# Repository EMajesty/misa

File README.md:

<h1 align="center">MISA</h1>

<p align="center">
68k SBC somewhat inspired by the Lisa and the Mac, and similar projects around the net.
</p>

<p align="center">
MC68HC000P16 (at 4/8/16 MHz)
<br />
1MB ROM (2x SST39SF040)
<br />
1MB SRAM (2x AS6C4008-55PCN)
<br />
ATF1508 CPLD for glue
<br />
UART
<br />
CF card
<br />
Monochrome display
<br />
Audio with YM2151?
<br />
Keyboard?
<br />
Wifi with WizFi360???
</p>

### TODO

- [ ] HW proto
- [ ] PLD logic
- [ ] Monitor program
- [ ] UART stuff
- [ ] Display stuff
- [x] Font 
- [ ] Input stuff
- [ ] FAT16/VFAT 
- [ ] File manager
- [ ] A beep
- [ ] Text editor
- [ ] Terminal emulator
- [ ] Lisp interpreter
- [ ] Doom
- [ ] ?????
- [ ] Multitasking kernel

### Docs

[68000 Hardware Manual](https://bitsavers.org/pdf/peripheralTechnology/68000_Hardware_Manual.pdf)

[M68000 User's Manual](https://www.nxp.com/docs/en/reference-manual/MC68000UM.pdf)

### BOM

| Ref | Part | Qty | Package | Datasheet | Notes |
|---|---|---|---|---|---|
||MC68HC000|1|DIP64/PLCC68|[Datasheet](https://igspgm.com/repairs/MC68HC000.pdf)|MPU|
||YM2151|1|DIP24|[Datasheet](https://retrocdn.net/images/1/1c/YM2151_datasheet.pdf)<br/>[Application manual](https://retrocdn.net/images/9/9c/YM2151_Application_Manual.pdf)|Sound|
||YM3012|1|DIP16|[Datasheet](https://datasheet4u.com/pdf-down/Y/M/3/YM3012-Yamaha.pdf)|DAC|
||TDA2822M|1|DIP8|[Datasheet](https://www.mouser.com/catalog/specsheets/stmicroelectronics_cd00000134.pdf)|Power amp|
||AS6C4008-55PCN|2|DIP32|[Datasheet](https://eu.mouser.com/datasheet/3/893/1/AS6C4008.pdf)|SRAM|
||SST39SF040|2|PLCC32|[Datasheet](https://ww1.microchip.com/downloads/aemDocuments/documents/MPD/ProductDocuments/DataSheets/SST39SF010A-SST39SF020A-SST39SF040-Data-Sheet-DS20005022.pdf)|ROM|
||ATF1508AS|1|PLCC84|[Datasheet](https://ww1.microchip.com/downloads/en/DeviceDoc/doc0784.pdf)|CPLD|
||MC68681FN|1|PLCC44|[Datasheet](https://www.microelectronicash.com/downloads/MC68681P.pdf)<br/>[AN-0899](https://www.bitsavers.org/components/motorola/_appNotes/AN-0899_A_Terminal_Interface,_Printer...for_an_MC68000-Based_System_using_the_MC68681_DUART.pdf)|DUART|
||NE555P|1|DIP8|[Datasheet](https://www.ti.com/lit/ds/symlink/se555.pdf?HQS=dis-dk-null-digikeymode-dsf-pf-null-wwe&ts=1771745013638&ref_url=https%253A%252F%252Fwww.ti.com%252Fgeneral%252Fdocs%252Fsuppproductinfo.tsp%253FdistId%253D10%2526gotoUrl%253Dhttps%253A%252F%252Fwww.ti.com%252Flit%252Fgpn%252Fse555)||
||SN74HC05N|1|DIP14|[Datasheet](https://www.ti.com/lit/ds/symlink/sn74hc05.pdf?HQS=dis-dk-null-digikeymode-dsf-pf-null-wwe&ts=1771768334330&ref_url=https%253A%252F%252Fwww.ti.com%252Fgeneral%252Fdocs%252Fsuppproductinfo.tsp%253FdistId%253D10%2526gotoUrl%253Dhttps%253A%252F%252Fwww.ti.com%252Flit%252Fgpn%252Fsn74hc05)||
||SN74HCT74N|1|DIP14|[Datasheet](https://www.ti.com/lit/ds/symlink/sn74hct74.pdf?HQS=dis-dk-null-digikeymode-dsf-pf-null-wwe&ts=1771757308194&ref_url=https%253A%252F%252Fwww.ti.com%252Fgeneral%252Fdocs%252Fsuppproductinfo.tsp%253FdistId%253D10%2526gotoUrl%253Dhttps%253A%252F%252Fwww.ti.com%252Flit%252Fgpn%252Fsn74hct74)||
||16 MHz oscillator|1|DIP8|[Datasheet](https://www.ctscorp.com/Files/DataSheets/Passives/FCP/Clock-Oscillators/clock-ocillators-MXO45_MXO45HS-datasheet.pdf)||
||3.6864 MHz oscillator|1|DIP8|[Datasheet](https://www.ctscorp.com/Files/DataSheets/Passives/FCP/Clock-Oscillators/clock-ocillators-MXO45_MXO45HS-datasheet.pdf)||
||WizFi360-CON|1||[Datasheet](https://docs.wiznet.io/pdf-viewer?file=%2Fassets%2Ffiles%2Fwizfi360_ds_v112_en-1495cb0bcb7e6583e492b1b8967f7fb4.pdf)|WIFI|
||5.7" 320240 RA8835|1||[Module](https://www.buydisplay.com/download/manual/ERM320240-1_Series_Datasheet.pdf)<br />[Controller](https://www.buydisplay.com/download/ic/RA8835.pdf)|Display|

### Memory map (RAM vectors + 2 MiB I/O)

| Region   | Start      | End        | Size   | Notes |
|---------|------------|------------|--------|-------|
| ROM     | 0x00000000 | 0x000FFFFF | 1 MiB  | 2x SST39SF040; contains reset vectors, monitor, bootloader; early startup runs from here. |
| Vectors | 0x00100000 | 0x001003FF | 1 KiB  | Vector table copied from ROM into RAM at boot; CPU configured to use RAM vectors.|
| RAM     | 0x00100000 | 0x001FFFFF | 1 MiB  | Same 1 MiB SRAM; low area holds vectors + kernel data, high end used for supervisor/user stacks and heap. |
| I/O     | 0x00E00000 | 0x00FFFFFF | 2 MiB  | CPLD‑decoded I/O window for UART, IDE/CF, keyboard, video, audio, WiFi, unused space.|
| Unused  | Everything else | -     | -      ||

### I/O submap (0x00E00000–0x00FFFFFF)

| Device   | CS        | Start      | End        | Size    | Bus width | Notes |
|---------|-----------|------------|------------|---------|-----------|-------|
| UART    | UART_CS   | 0x00E00000 | 0x00E00FFF | 4 KiB   | 8‑bit     | MC68681FN on D0–D7, RS0–RS3 from CPU A1–A4.|
| IDE / CF| IDE_CS0/1 | 0x00E01000 | 0x00E01FFF | 4 KiB   | 16‑bit    | 16‑bit data path via CPLD, command/control regs.|
| Keyboard| KBD_CS    | 0x00E02000 | 0x00E02FFF | 4 KiB   | 8‑bit     | Simple DATA/STATUS/CONTROL registers.|
| Video   | VID_CS    | 0x00E03000 | 0x00E03FFF | 4 KiB   | 8‑ or 16‑bit | RA8835 controller regs; framebuffer mapped elsewhere or via paging.|
| Audio   | AUD_CS    | 0x00E04000 | 0x00E04FFF | 4 KiB   | 8‑bit     | YM2151 register interface; DAC/analog path is fixed hardware, no CPU control.|
| WiFi    | WIFI_CS   | 0x00E05000 | 0x00E05FFF | 4 KiB   | 8‑bit     | WizFi360 memory‑mapped UART/command regs (future). |
| Unused  | –         | 0x00E06000 | 0x00FFFFFF | ~1.97 MiB | 8‑ or 16‑bit ||

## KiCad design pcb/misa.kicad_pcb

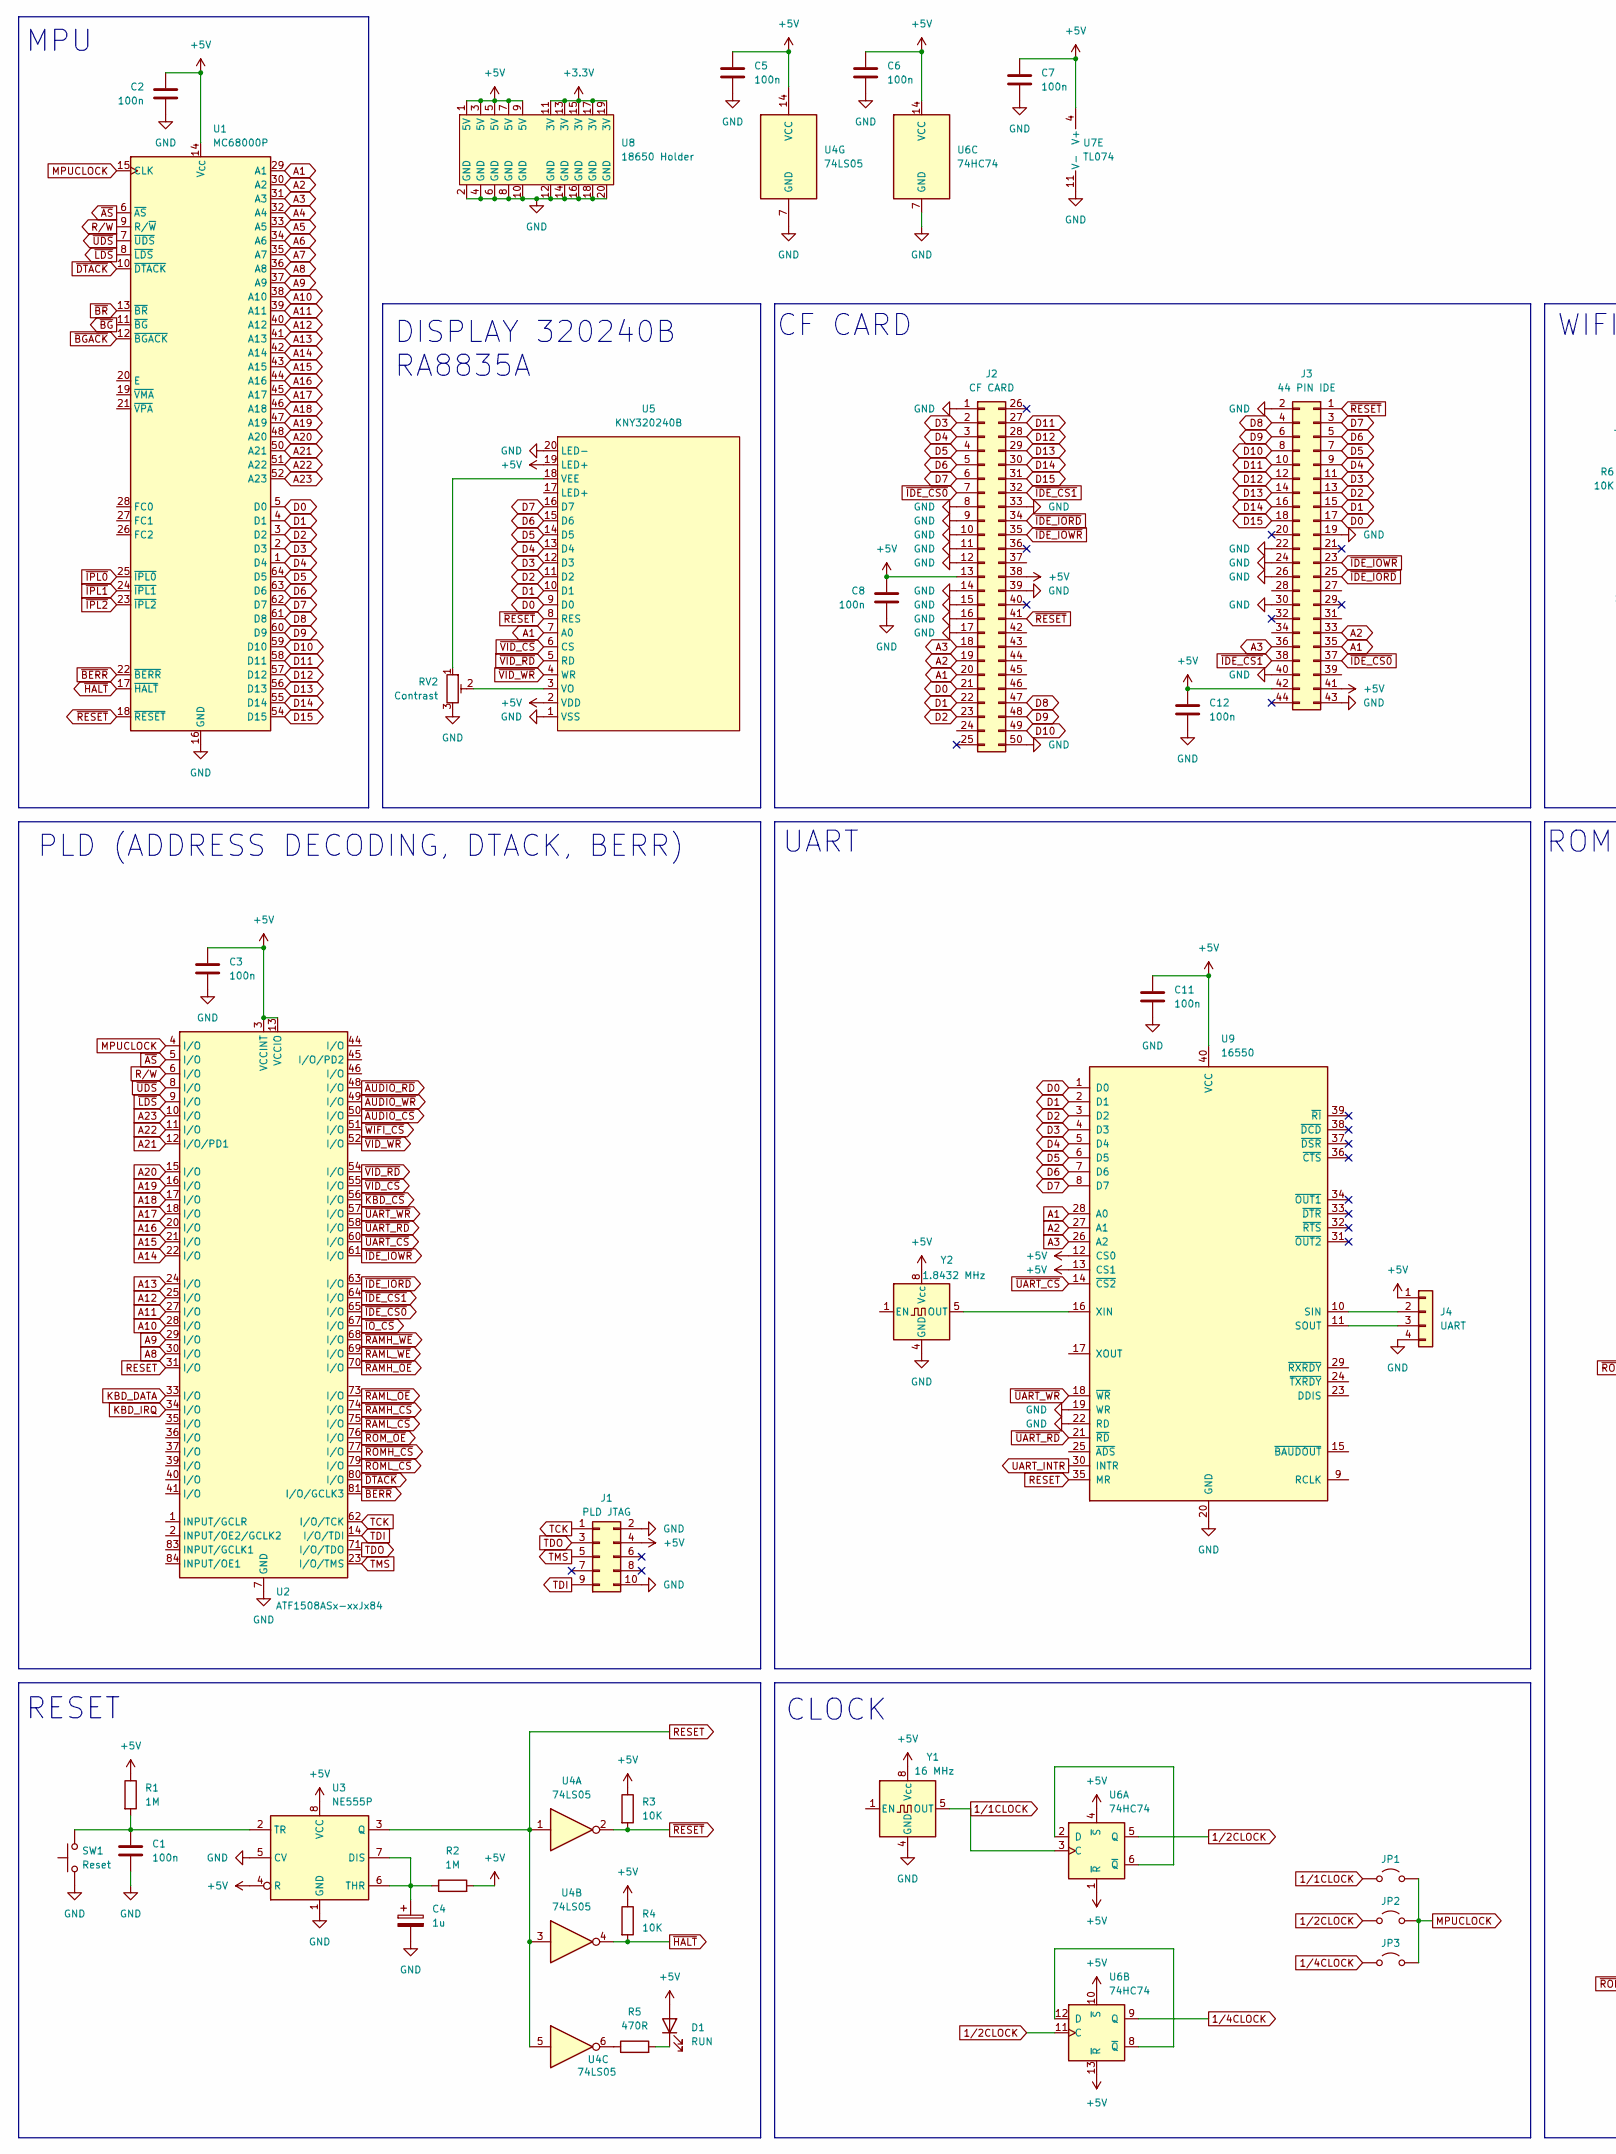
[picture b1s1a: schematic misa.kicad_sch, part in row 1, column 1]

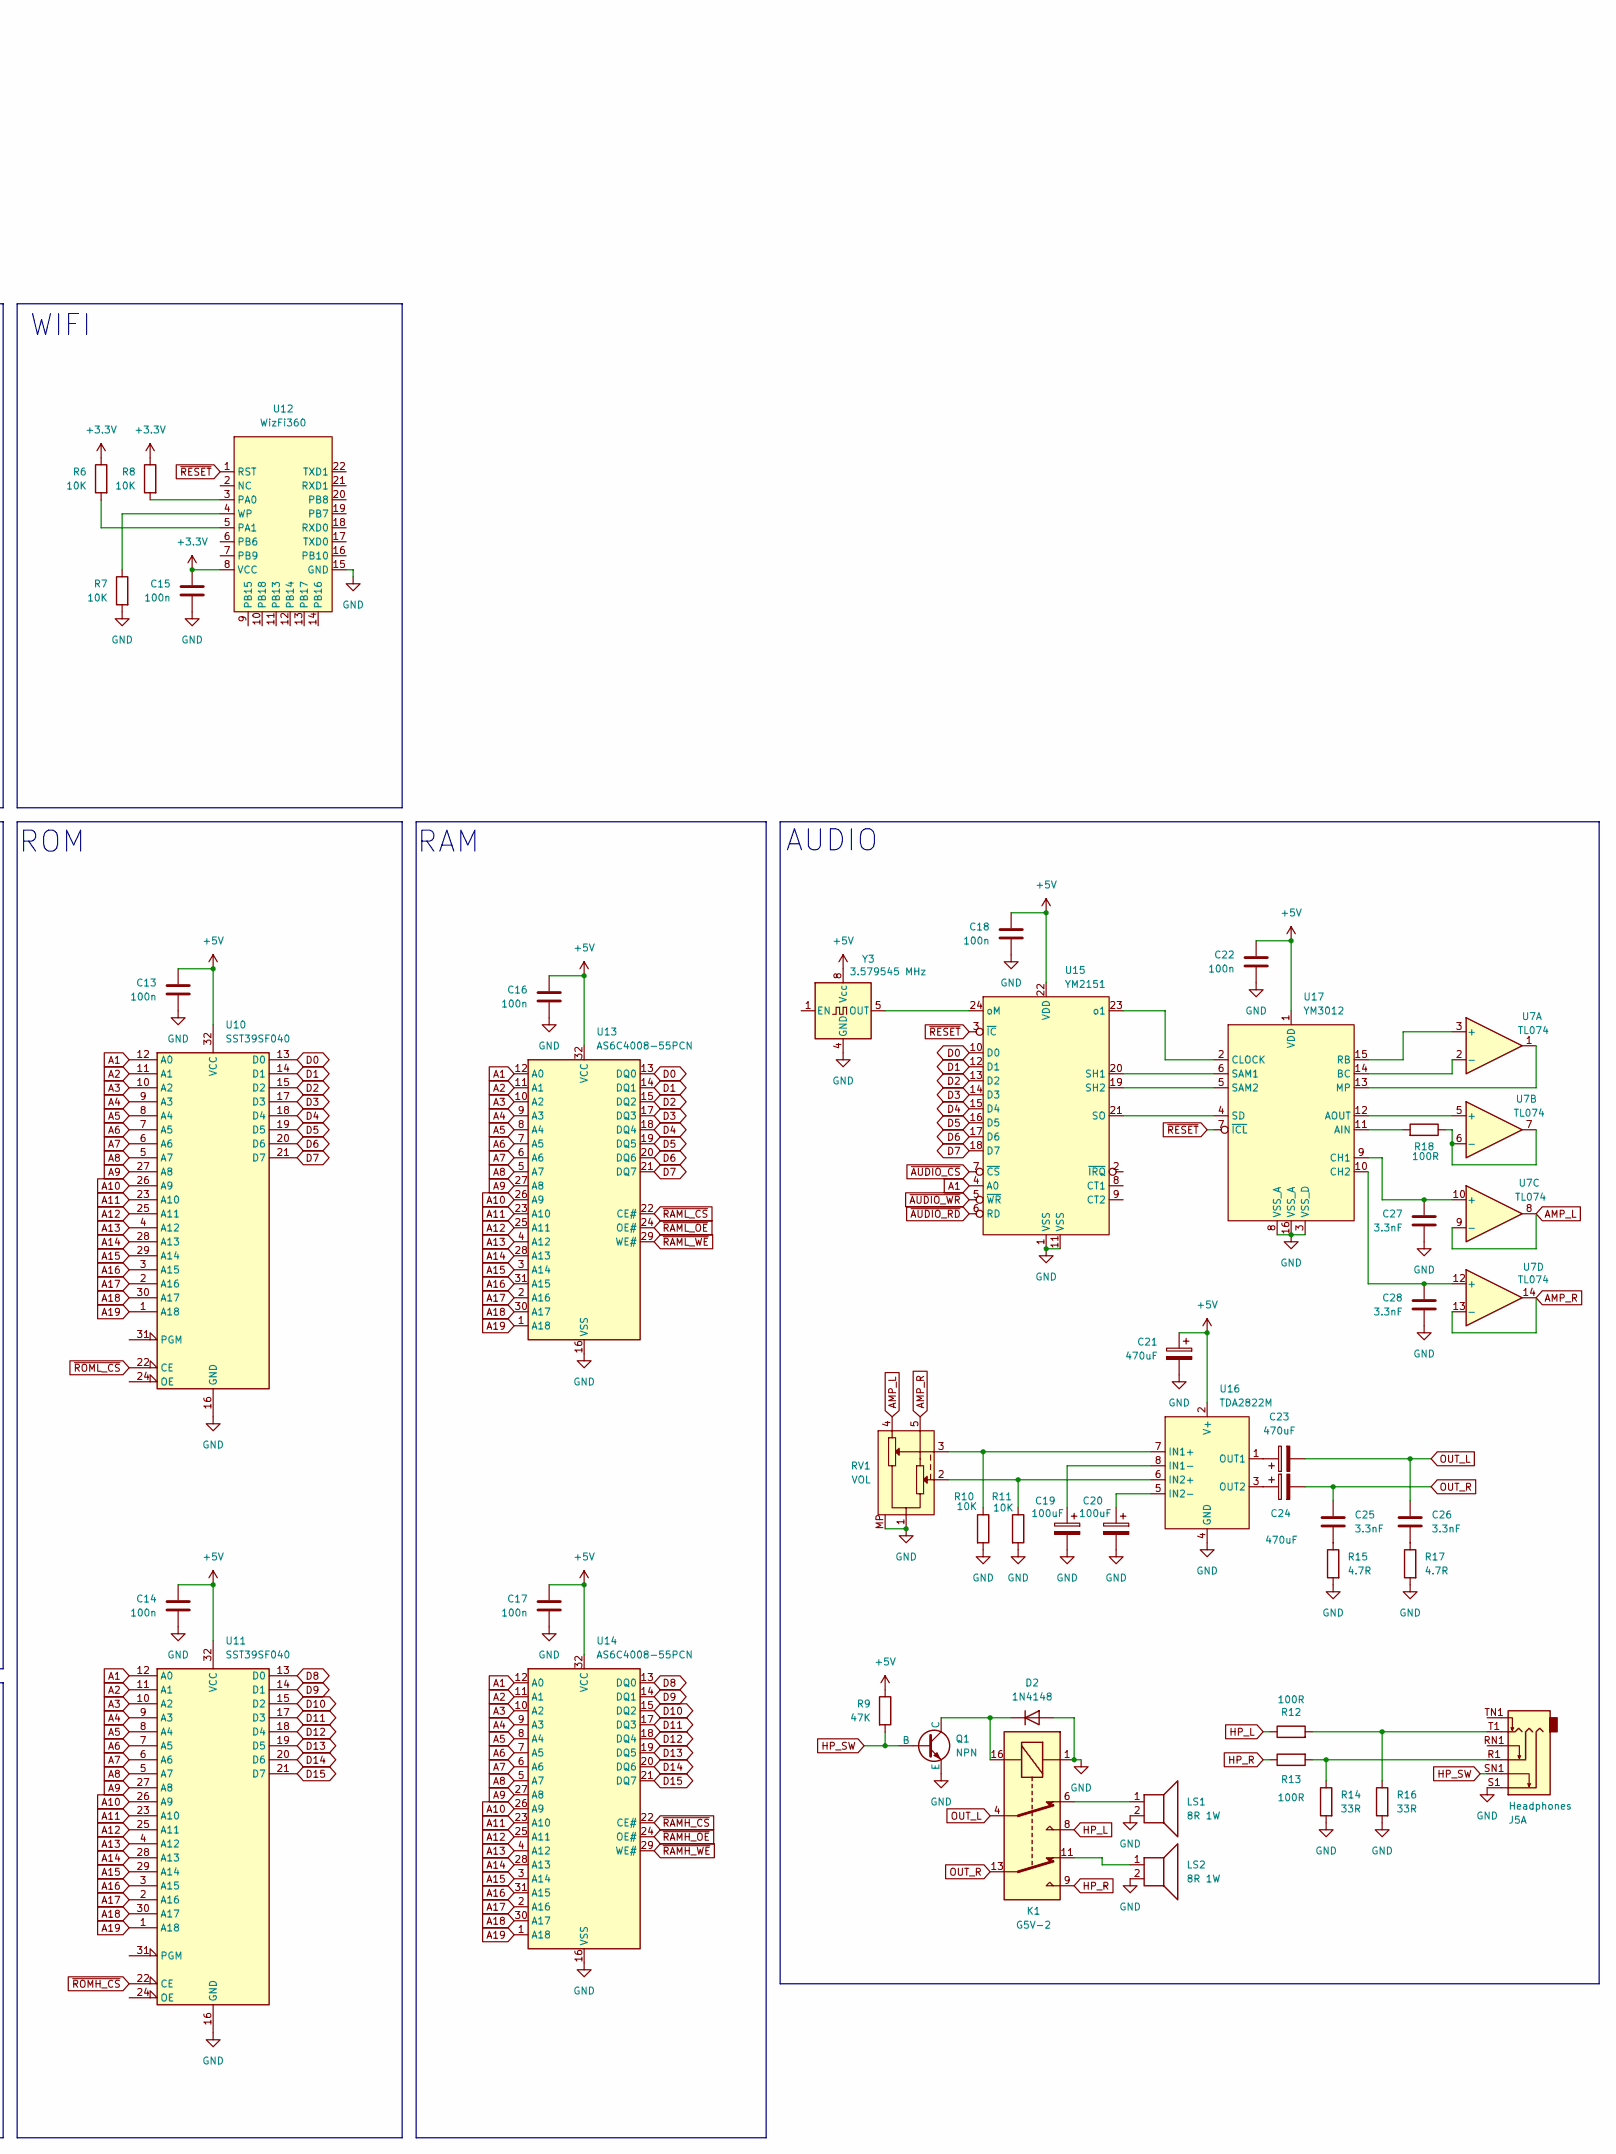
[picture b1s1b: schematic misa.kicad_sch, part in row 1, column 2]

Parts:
C1, C2, C3, C5, C6, C7, C8, C11, C12, C13, C14, C15, C16, C17, C18, C22: 100n; C_Rect_L7.0mm_W2.5mm_P5.00mm
C4: 1u; CP_Radial_D4.0mm_P2.00mm
C19, C20: 100uF; CP_Radial_D5.0mm_P2.50mm
C21, C23, C24: 470uF; CP_Radial_D6.3mm_P2.50mm
C25, C26, C27, C28: 3.3nF; C_Rect_L7.0mm_W2.5mm_P5.00mm
D1: RUN; LED_D3.0mm
D2: 1N4148; D_DO-35_SOD27_P7.62mm_Horizontal
J1: PLD JTAG; Pins_2x05_2.54mm_TH; Part Number 1-1002FBV0T
J2: CF CARD; CF_Card_Socket_PTH
J3: 44 PIN IDE; PinSocket_2x22_P2.54mm_Vertical
J4: UART; Pins_1x04_2.54mm_TH_SWD; Part Number 1-0401FBV0T
J5: Headphones; Jack_6.35mm_Neutrik_NMJ6HFD2-AU_Horizontal
JP1, JP2, JP3: Jumper_2_Open; PinHeader_1x02_P2.54mm_Vertical
K1: G5V-2; Relay_DPDT_Omron_G5V-2
LS1, LS2: 8R 1W; PinHeader_1x02_P2.54mm_Vertical
Q1: NPN; TO-92L_Inline_Wide
R1, R2: 1M; R_Axial_DIN0207_L6.3mm_D2.5mm_P7.62mm_Horizontal
R3, R4, R6, R7, R8, R10, R11: 10K; R_Axial_DIN0207_L6.3mm_D2.5mm_P7.62mm_Horizontal
R5: 470R; R_Axial_DIN0207_L6.3mm_D2.5mm_P7.62mm_Horizontal
R9: 47K; R_Axial_DIN0207_L6.3mm_D2.5mm_P7.62mm_Horizontal
R12, R13, R18: 100R; R_Axial_DIN0207_L6.3mm_D2.5mm_P7.62mm_Horizontal
R14, R16: 33R; R_Axial_DIN0207_L6.3mm_D2.5mm_P7.62mm_Horizontal
R15, R17: 4.7R; R_Axial_DIN0207_L6.3mm_D2.5mm_P7.62mm_Horizontal
RV1: VOL
RV2: Contrast
SW1: Reset
U1: MC68000P; PLCC-68_THT-Socket
U2: ATF1508ASx-xxJx84; PLCC-84_THT-Socket
U3: NE555P; DIP-8_W7.62mm
U4: 74LS05; DIP-14_W7.62mm_Socket_LongPads
U5: KNY320240B
U6: 74HC74; DIP-14_W7.62mm_Socket_LongPads
U7: TL074; DIP-14_W7.62mm_Socket_LongPads
U8: 18650 Holder; 18650_holder
U9: 16550; PLCC-44_THT-Socket
U10, U11: SST39SF040; PLCC-32_THT-Socket
U12: WizFi360; Untitled
U13, U14: AS6C4008-55PCN; DIP-32_W15.24mm
U15: YM2151; DIP-24_18.0mmx34.29mm_W15.24mm_Socket_LongPads
U16: TDA2822M; DIP-8_W7.62mm_Socket_LongPads
U17: YM3012; DIP-16_W7.62mm_Socket_LongPads
Y1: 16 MHz; Oscillator_DIP-8
Y2: 1.8432 MHz; Oscillator_DIP-8
Y3: 3.579545 MHz; Oscillator_DIP-8

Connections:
1/1CLOCK: JP1.1 (A), U6.3 (C), Y1.5 (OUT)
1/2CLOCK: JP2.1 (A), U6.5 (Q), U6.11 (C)
1/4CLOCK: JP3.1 (A), U6.9 (Q)
+3.3V: C15.1, R6.1, R8.1, U8.11 (3V), U8.13 (3V), U8.15 (3V), U8.17 (3V), U8.19 (3V), U12.8 (VCC)
+5V: C2.1, C3.1, C5.1, C6.1, C7.1, C8.1, C11.1, C12.1, C13.1, C14.1, C16.1, C17.1, C18.1, C21.1, C22.1, D1.2 (A), J1.4 (GND), J2.13, J2.38, J3.41, J3.42, J4.1, R1.1, R2.2, R3.1, R4.1, R9.1, U1.14 (V_{CC}), U1.49 (V_{CC}), U2.3 (VCCINT), U2.13 (VCCIO), U2.26 (VCCIO), U2.38 (VCCIO), U2.43 (VCCINT), U2.53 (VCCIO), U2.66 (VCCIO), U2.78 (VCCIO), U3.4 (R), U3.8 (VCC), U4.14 (VCC), U5.2 (VDD), U5.19 (LED+), U6.1 (~R), U6.4 (~S), U6.10 (~S), U6.13 (~R), U6.14 (VCC), U7.4 (V+), U8.1 (5V), U8.3 (5V), U8.5 (5V), U8.7 (5V), U8.9 (5V), U9.12 (CS0), U9.13 (CS1), U9.40 (VCC), U10.32 (VCC), U11.32 (VCC), U13.32 (VCC), U14.32 (VCC), U15.22 (VDD), U16.2 (V+), U17.1 (VDD), Y1.8 (Vcc), Y2.8 (Vcc), Y3.8 (Vcc)
A1: J2.20, J3.35, U1.29 (A1), U5.7 (A0), U9.28 (A0), U10.12 (A0), U11.12 (A0), U13.12 (A0), U14.12 (A0), U15.4 (A0)
A2: J2.19, J3.33, U1.30 (A2), U9.27 (A1), U10.11 (A1), U11.11 (A1), U13.11 (A1), U14.11 (A1)
A3: J2.18, J3.36, U1.31 (A3), U9.26 (A2), U10.10 (A2), U11.10 (A2), U13.10 (A2), U14.10 (A2)
A4: U1.32 (A4), U10.9 (A3), U11.9 (A3), U13.9 (A3), U14.9 (A3)
A5: U1.33 (A5), U10.8 (A4), U11.8 (A4), U13.8 (A4), U14.8 (A4)
A6: U1.34 (A6), U10.7 (A5), U11.7 (A5), U13.7 (A5), U14.7 (A5)
A7: U1.35 (A7), U10.6 (A6), U11.6 (A6), U13.6 (A6), U14.6 (A6)
A8: U1.36 (A8), U2.30 (I/O), U10.5 (A7), U11.5 (A7), U13.5 (A7), U14.5 (A7)
A9: U1.37 (A9), U2.29 (I/O), U10.27 (A8), U11.27 (A8), U13.27 (A8), U14.27 (A8)
A10: U1.38 (A10), U2.28 (I/O), U10.26 (A9), U11.26 (A9), U13.26 (A9), U14.26 (A9)
A11: U1.39 (A11), U2.27 (I/O), U10.23 (A10), U11.23 (A10), U13.23 (A10), U14.23 (A10)
A12: U1.40 (A12), U2.25 (I/O), U10.25 (A11), U11.25 (A11), U13.25 (A11), U14.25 (A11)
A13: U1.41 (A13), U2.24 (I/O), U10.4 (A12), U11.4 (A12), U13.4 (A12), U14.4 (A12)
A14: U1.42 (A14), U2.22 (I/O), U10.28 (A13), U11.28 (A13), U13.28 (A13), U14.28 (A13)
A15: U1.43 (A15), U2.21 (I/O), U10.29 (A14), U11.29 (A14), U13.3 (A14), U14.3 (A14)
A16: U1.44 (A16), U2.20 (I/O), U10.3 (A15), U11.3 (A15), U13.31 (A15), U14.31 (A15)
A17: U1.45 (A17), U2.18 (I/O), U10.2 (A16), U11.2 (A16), U13.2 (A16), U14.2 (A16)
A18: U1.46 (A18), U2.17 (I/O), U10.30 (A17), U11.30 (A17), U13.30 (A17), U14.30 (A17)
A19: U1.47 (A19), U2.16 (I/O), U10.1 (A18), U11.1 (A18), U13.1 (A18), U14.1 (A18)
A20: U1.48 (A20), U2.15 (I/O)
A21: U1.50 (A21), U2.12 (I/O/PD1)
A22: U1.51 (A22), U2.11 (I/O)
A23: U1.52 (A23), U2.10 (I/O)
AMP_L: RV1.4, U7.8, U7.9 (-)
AMP_R: RV1.5, U7.13 (-), U7.14
D0: J2.21, J3.17, U1.5 (D0), U5.9 (D0), U9.1 (D0), U10.13 (D0), U13.13 (DQ0), U15.10 (D0)
D1: J2.22, J3.15, U1.4 (D1), U5.10 (D1), U9.2 (D1), U10.14 (D1), U13.14 (DQ1), U15.12 (D1)
D2: J2.23, J3.13, U1.3 (D2), U5.11 (D2), U9.3 (D2), U10.15 (D2), U13.15 (DQ2), U15.13 (D2)
D3: J2.2, J3.11, U1.2 (D3), U5.12 (D3), U9.4 (D3), U10.17 (D3), U13.17 (DQ3), U15.14 (D3)
D4: J2.3, J3.9, U1.1 (D4), U5.13 (D4), U9.5 (D4), U10.18 (D4), U13.18 (DQ4), U15.15 (D4)
D5: J2.4, J3.7, U1.64 (D5), U5.14 (D5), U9.6 (D5), U10.19 (D5), U13.19 (DQ5), U15.16 (D5)
D6: J2.5, J3.5, U1.63 (D6), U5.15 (D6), U9.7 (D6), U10.20 (D6), U13.20 (DQ6), U15.17 (D6)
D7: J2.6, J3.3, U1.62 (D7), U5.16 (D7), U9.8 (D7), U10.21 (D7), U13.21 (DQ7), U15.18 (D7)
D8: J2.47, J3.4, U1.61 (D8), U11.13 (D0), U14.13 (DQ0)
D9: J2.48, J3.6, U1.60 (D9), U11.14 (D1), U14.14 (DQ1)
D10: J2.49, J3.8, U1.59 (D10), U11.15 (D2), U14.15 (DQ2)
D11: J2.27, J3.10, U1.58 (D11), U11.17 (D3), U14.17 (DQ3)
D12: J2.28, J3.12, U1.57 (D12), U11.18 (D4), U14.18 (DQ4)
D13: J2.29, J3.14, U1.56 (D13), U11.19 (D5), U14.19 (DQ5)
D14: J2.30, J3.16, U1.55 (D14), U11.20 (D6), U14.20 (DQ6)
D15: J2.31, J3.18, U1.54 (D15), U11.21 (D7), U14.21 (DQ7)
GND: C1.2, C2.2, C3.2, C4.2, C5.2, C6.2, C7.2, C8.2, C11.2, C12.2, C13.2, C14.2, C15.2, C16.2, C17.2, C18.2, C19.2, C20.2, C21.2, C22.2, C27.2, C28.2, D2.2 (A), J1.2 (+12V), J1.10 (-12V), J2.1, J2.8, J2.9, J2.10, J2.11, J2.12, J2.14, J2.15, J2.16, J2.17, J2.33, J2.39, J2.50, J3.2, J3.19, J3.22, J3.24, J3.26, J3.30, J3.40, J3.43, J4.4, J5.S1, K1.1, LS1.2, LS2.2, Q1.3 (E), R7.2, R10.2, R11.2, R14.2, R15.2, R16.2, R17.2, RV1.1, RV1.MP, RV2.3, SW1.1, U1.16 (GND), U1.53 (GND), U2.7 (GND), U2.19 (GND), U2.32 (GND), U2.42 (GND), U2.47 (GND), U2.59 (GND), U2.72 (GND), U2.82 (GND), U3.1 (GND), U3.5 (CV), U4.7 (GND), U5.1 (VSS), U5.20 (LED-), U6.7 (GND), U7.11 (V-), U8.2 (GND), U8.4 (GND), U8.6 (GND), U8.8 (GND), U8.10 (GND), U8.12 (GND), U8.14 (GND), U8.16 (GND), U8.18 (GND), U8.20 (GND), U9.19 (WR), U9.20 (GND), U9.22 (RD), U10.16 (GND), U11.16 (GND), U12.15 (GND), U13.16 (VSS), U14.16 (VSS), U15.1 (VSS), U15.11 (VSS), U16.4 (GND), U17.3 (VSS_D), U17.8 (VSS_A), U17.16 (VSS_A), Y1.4 (GND), Y2.4 (GND), Y3.4 (GND)
HP_L: K1.8, R12.1
HP_R: K1.9, R13.1
HP_SW: J5.SN1, Q1.2 (B), R9.2
KBD_DATA: U2.33 (I/O)
KBD_IRQ: U2.34 (I/O)
MPUCLOCK: JP1.2 (B), JP2.2 (B), JP3.2 (B), U1.15 (CLK), U2.4 (I/O)
unnamed: C25.2, R15.1
unnamed: C26.2, R17.1
unnamed: D1.1 (K), R5.2
unnamed: D2.1 (K), K1.16, Q1.1 (C)
unnamed: J4.2, U9.10 (SIN)
unnamed: J4.3, U9.11 (SOUT)
unnamed: J5.R1, R13.2, R14.1
unnamed: J5.T1, R12.2, R16.1
unnamed: K1.6, LS1.1
unnamed: K1.11, LS2.1
unnamed: R5.1, U4.6
unnamed: RV2.1, U5.18 (VEE)
unnamed: RV2.2, U5.3 (VO)
unnamed: C4.1, R2.1, U3.6 (THR), U3.7 (DIS)
unnamed: C1.1, R1.2, SW1.2, U3.2 (TR)
unnamed: U6.2 (D), U6.6 (~Q)
unnamed: U6.8 (~Q), U6.12 (D)
unnamed: R18.1, U7.6 (-), U7.7
unnamed: U9.16 (XIN), Y2.5 (OUT)
unnamed: R8.2, U12.3 (PA0)
unnamed: R6.2, U12.5 (PA1)
unnamed: R7.1, U12.4 (WP)
unnamed: U15.20 (SH1), U17.6 (SAM1)
unnamed: U15.19 (SH2), U17.5 (SAM2)
unnamed: U15.21 (SO), U17.4 (SD)
unnamed: U15.23 (o1), U17.2 (CLOCK)
unnamed: U15.24 (oM), Y3.5 (OUT)
unnamed: R10.1, RV1.3, U16.7 (IN1+)
unnamed: C19.1, U16.8 (IN1-)
unnamed: R11.1, RV1.2, U16.6 (IN2+)
unnamed: C20.1, U16.5 (IN2-)
unnamed: C23.1, U16.1 (OUT1)
unnamed: C24.1, U16.3 (OUT2)
unnamed: R18.2, U17.11 (AIN)
unnamed: U7.5 (+), U17.12 (AOUT)
unnamed: U7.2 (-), U17.14 (BC)
unnamed: C27.1, U7.10 (+), U17.9 (CH1)
unnamed: C28.1, U7.12 (+), U17.10 (CH2)
unnamed: U7.1, U17.13 (MP)
unnamed: U7.3 (+), U17.15 (RB)
OUT_L: C23.2, C26.1, K1.4
OUT_R: C24.2, C25.1, K1.13
RESET: U2.31 (I/O), U3.3 (Q), U4.1, U4.3, U4.5, U9.35 (MR)
R/W: U1.9 (R/~W), U2.6 (I/O)
TCK: J1.1 (+12V), U2.62 (I/O/TCK)
TDI: J1.9 (-12V), U2.14 (I/O/TDI)
TDO: J1.3 (GND), U2.71 (I/O/TDO)
TMS: J1.5 (GND), U2.23 (I/O/TMS)
UART_INTR: U9.30 (INTR)
~AS: U1.6 (~AS), U2.5 (I/O)
~AUDIO_CS: U2.50 (I/O), U15.7 (~CS)
~AUDIO_RD: U2.48 (I/O), U15.6 (RD)
~AUDIO_WR: U2.49 (I/O), U15.5 (~WR)
~BERR: U1.22 (~BERR), U2.81 (I/O/GCLK3)
~BGACK: U1.12 (~BGACK)
~BG: U1.11 (~BG)
~BR: U1.13 (~BR)
~DTACK: U1.10 (~DTACK), U2.80 (I/O)
~HALT: R4.2, U1.17 (~HALT), U4.4
~IDE_CS0: J2.7, J3.37, U2.65 (I/O)
~IDE_CS1: J2.32, J3.38, U2.64 (I/O)
~IDE_IORD: J2.34, J3.25, U2.63 (I/O)
~IDE_IOWR: J2.35, J3.23, U2.61 (I/O)
~IO_CS: U2.67 (I/O)
~IPL0: U1.25 (~IPL0)
~IPL1: U1.24 (~IPL1)
~IPL2: U1.23 (~IPL2)
~KBD_CS: U2.56 (I/O)
~LDS: U1.8 (~LDS), U2.9 (I/O)
~RAMH_CS: U2.74 (I/O), U14.22 (CE#)
~RAMH_OE: U2.70 (I/O), U14.24 (OE#)
~RAMH_WE: U2.68 (I/O), U14.29 (WE#)
~RAML_CS: U2.75 (I/O), U13.22 (CE#)
~RAML_OE: U2.73 (I/O), U13.24 (OE#)
~RAML_WE: U2.69 (I/O), U13.29 (WE#)
~RESET: J2.41, J3.1, R3.2, U1.18 (~RESET), U4.2, U5.8 (RES), U12.1 (RST), U15.3 (~IC), U17.7 (~ICL)
~ROMH_CS: U2.77 (I/O), U11.22 (CE)
~ROML_CS: U2.79 (I/O), U10.22 (CE)
~ROM_OE: U2.76 (I/O)
~UART_CS: U2.60 (I/O), U9.14 (~CS2)
~UART_RD: U2.58 (I/O), U9.21 (~RD)
~UART_WR: U2.57 (I/O), U9.18 (~WR)
~UDS: U1.7 (~UDS), U2.8 (I/O)
~VID_CS: U2.55 (I/O), U5.6 (CS)
~VID_RD: U2.54 (I/O), U5.5 (RD)
~VID_WR: U2.52 (I/O), U5.4 (WR)
~WIFI_CS: U2.51 (I/O)

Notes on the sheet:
CF CARD
AUDIO
DISPLAY 320240B RA8835A
RESET
UART
RAM
ROM
MPU
PLD (ADDRESS DECODING, DTACK, BERR)
WIFI
CLOCK

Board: 2 copper layers, 78 parts (2 on the bottom side), 125 nets, no tracks yet.

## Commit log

2026-02-21 init
2026-02-21 gitignore
2026-02-21 cleanup
2026-02-21 readme
2026-02-21 mega stuff
2026-02-23 stuff
2026-02-23 testing stuff
2026-02-27 hell world
2026-03-01 mockup
2026-03-01 ethernet controller
2026-03-01 notes
2026-03-02 wifi
2026-03-02 todo
